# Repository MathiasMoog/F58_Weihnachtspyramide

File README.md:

# Antrieb und LED-Kerzen für Weihnachtspyramide

Und als kurzes Video: [Weihnachtspyramide](Bilder/Pyramide.mp4)

## Kurzfassung

Ein Arduino Nano ESP steuert den Antrieb und die LED Kerzen einer Weihnachtspyramide.

Über den ESP wird eine MQTT Anbindung erstellt.

### Hintergrund

Unsere Weihnachtspyramide ist seit einigen Jahren nicht mehr genutzt worden, da niemand Lust hat auf die echten Kerzen aufzupassen. Außerdem läuft sie mit den Kerzen nicht so gut.

In der Bastelkiste hatte ich noch einen (uralten) [Arduino Nano ESP](https://iot.fkainka.de/board) von F. Kainka und aus dem alten Drucker den Antrieb für die Scan Einheit.

### Ordner

- Bilder - Bilder und Zeichnungen
- Druckvorlagen - OpenSCAD Zeichnungen für 3D Drucke 
- PyramidenMQTT - Der Arduino Sketch 
- PyramidenSchaltplan - KiCad Schaltplan und Platine

## Aufbau

Passt es für eure Weihnachtspyramide an, dieser Abschnitt bezieht sich auf meine Pyramide.

### Antrieb 

Mit einem Motor aus der Bastelkiste probiert. Alter Antriebsmotor aus Scanner mit Getriebe. Blech zurecht gesägt. Optische Drehzahlerfassung entfernt. Anstelle Zahnräder, einen Gummiring verwendet. Letztes Zahnrad am Motor geschliffen so dass eine Laufrille für den Gummiring entsteht.  

Adapter von Antriebsstange über Antriebsrad bis Aufnahme in Kugellager, [Antrieb](Druckvorlagen/Antrieb.scad), und eine Kugellager Halterung,[Grundplatte](Druckvorlagen/Grundplatte.scad),  in OpenScad gezeichnet. Druck in PETG. Material ist guter Kompromiss zwischen leicht auf dem alten Creatity Ender druckbar und ausreichender Festigkeit. 

Antrieb                    |  Grundplatte
:-------------------------:|:-------------------------:
 | 

Der neue Antrieb ersetzt die alte Lagerung in einer Keramikschale.

Vorher                    |  Nachher
:-------------------------:|:-------------------------:
 | 

### Ansteuerung des Motors
  
Der Motor läuft ab 2,5 V an. Bilde 0 bis 100 auf 0 + [128, 255] ab. Er nimmt maximal 80 mA auf. Es reicht ein kleiner Transistor zum Schalten.

Aus Bastelkiste BC 639, 1 A maximal, gemessen Verstärkung hFE 100, Datenblatt mindestens 25 bei 5 mA Basisstrom. Auslegung, 560 Ohm Vorwiderstand

### Kerzen

Auf Thingiverse habe ich Kerzen mit schön gestalteten Flammen gefunden. Sie sind Teil eines Weihnachtsbogens [Christmas Light Bow](https://www.thingiverse.com/thing:4674237) von M. Lachmann. Flamme.stl mit transparentem PLA und die Kerzen in weißem PLA gedruckt. 

Kerze.stl hat Original 10 mm Durchmesser. Ich benötige 13 mm. Skaliere in x und y Richtung um 130 %. In x Richtung Skalierung 70, 80, 90, 100, 110, 120 %. Sieht nach ungleichmäßig abgebrannten Kerzen aus.

Löcher in die original Kerzenhalter gebohrt und Kabel durchgeführt:

Kabelführung                    |  Fertige Kerzen
:-------------------------:|:-------------------------:
 | 

An der Pyramide habe ich die Aussparungen für die Kerzenhalter mit einer Feile um deine Kabeldurchführung vergrößert.

Helle orange LEDs mit 5 mm Druchmesser im Vorrat entdeckt. Mit denen ergibt sich ein warmes Kerzenlicht. Jede LED mit zweiadrigem Kabel (Altes Flachbahn Kabel von Floppy) und 2,5 mm Stecker anbinden.

Vermessen 2,07 V bei 20 mA. Gewählt, 150 Ohm Vorwidderstand bei 5 V Versorgung und 0,5 V Spannungsabfall im ATMEGA.

## Schaltplan und Platine

Die Schaltung ist recht einfach. Motor und LEDs werden mit 5 V aus dem Arduino betrieben.

Aufgebaut habe ich es auf einem Stück Lochraster Platine

Der USB Anschluss und der Taster zur Bedienung ragen etwas unter dem Holzrahmen der Pyramide hervor. Mit dem Taster lassen sich die Kerzen und der Motor ein- und ausschalten.

## Arduino Sketch

Im Code erklärt: [PyramidenMqtt](PyramidenMqtt/PyramidenMqtt.ino)

Die NanoESP Boards sind schon sehr betagt, aber es funktioniert immer noch. Ich habe zwei Anpassungen an der NanoESP Bibliothek vorgenommen: Messages zuschneiden und obsolete subscribe events bei disconnect löschen. Getestet habe ich mit meinem Fork der [NanoESP Bibliothek](https://github.com/MathiasMoog/NanoESP)

Damit 6 LEDs und der Motor per PWM angesteuert werden können, nutze ich für die LEDs die [SoftPWM Bibliothek](https://github.com/bhagman/SoftPWM) von B. Hagman.

Die Konfiguration erfolgt in secrets.h. Eingecheckt ist nur die secretsVorlage.h. In secrets.h umbenennen und anpassen.

## Einbindung in die Hausautomation

Ich nutze [openHAB](https://www.openhab.org/) mit einer textuellen Konfiguration.

Hier die Thing Definition

    Thing mqtt:topic:weihnachtspyramide "Weihnachtspyramide" (mqtt:broker:myBroker) {
      Channels:
      // Motor als Dimmer, 0..100
      Type dimmer : motor "Motor" [ stateTopic="openhab/pyramide/motor/state", commandTopic="openhab/pyramide/motor/set", min=0, max=100, step=1 ]
      // Kerzen als Switch, ON / OFF
      Type switch : kerzen "Kerzen" [ stateTopic="openhab/pyramide/kerzen/state", commandTopic="openhab/pyramide/kerzen/set" ]
    } 
	
Diese gehört in eine Bridge hinein die die Verbindung zu dem MQTT broker beinhaltet.

Die Items zu den beiden channels:

    Group gMqttWeihnachtspyramide "Weihnachtspyramide" <network> (gEG_Buero)

    /* Motor der Weihnachtspyramide.
        Dimmer 0..100
        0 = Aus
        1 = Anlauf, ca. 2.5 V
        100 = Voll an
    */    
    Dimmer PyramideMotor "Motor [%d]" <network> (gMqttWeihnachtspyramide) 
      { channel="mqtt:topic:weihnachtspyramide:motor" }

    /* Kerzen der Weihnachtspyramide.
        Switch Ein/Aus, flackern sobald ein.
    */
    Switch PyramideKerzen "Kerzen" <network> (gMqttWeihnachtspyramide) 
      { channel="mqtt:topic:weihnachtspyramide:kerzen" }

So lässt sich alles vom Handy aus bedienen und die LEDs gehen mit der restlichen Weihnachtsbeleuchtung automatisch an.

## Testen

Zum Testen - und für den Betrieb - wird ein MQTT broker benötigt. Ich verwende den [Mosquitto broker](https://mosquitto.org/) von Eclipse.

Es hat etwas gedauert bis ich eine stabile Lösung mit automatischen Neu-Verbindungen zum WiFi und MQTT beisammen hatte. Ein Blick in die Mosquitto Logs hilft ...

    sudo tail -f /var/log/mosquitto/mosquitto.log

Mittlerweile gehen nur noch sehr selten (während reconnect) MQTT messages verloren, ggf. Prüfen

    mosquitto_sub -h xxx -u xxx -P xxx -t openhab/pyramide/#

## Nachbau

Den NanoESP gibt es schon länger nicht mehr. Der Arduino Nano ESP 32 ist nahezu Pin-Kompatibel. Zu beachten ist:

- Er arbeitet mit 3.3 V, ggf. die LED Vorwiderstände anpassen 
- Mein Motor benötigt 5 V, die können von USB übernommen werden
- Die SoftPWM Bibliothek ist nicht mehr notwendig
- Es wird ein anderer MQTT Client benötigt, z.B. ArduinoMqttClient

Umgesetzt habe ich es nicht, hier ein MQTT Beispiel mit dem Nano ESP 32: [MQTT LED](https://gitlab.com/MathiasMoog/L20_MqttLed)

Ansonsten irgendein günstiges ESP 32 Board ...

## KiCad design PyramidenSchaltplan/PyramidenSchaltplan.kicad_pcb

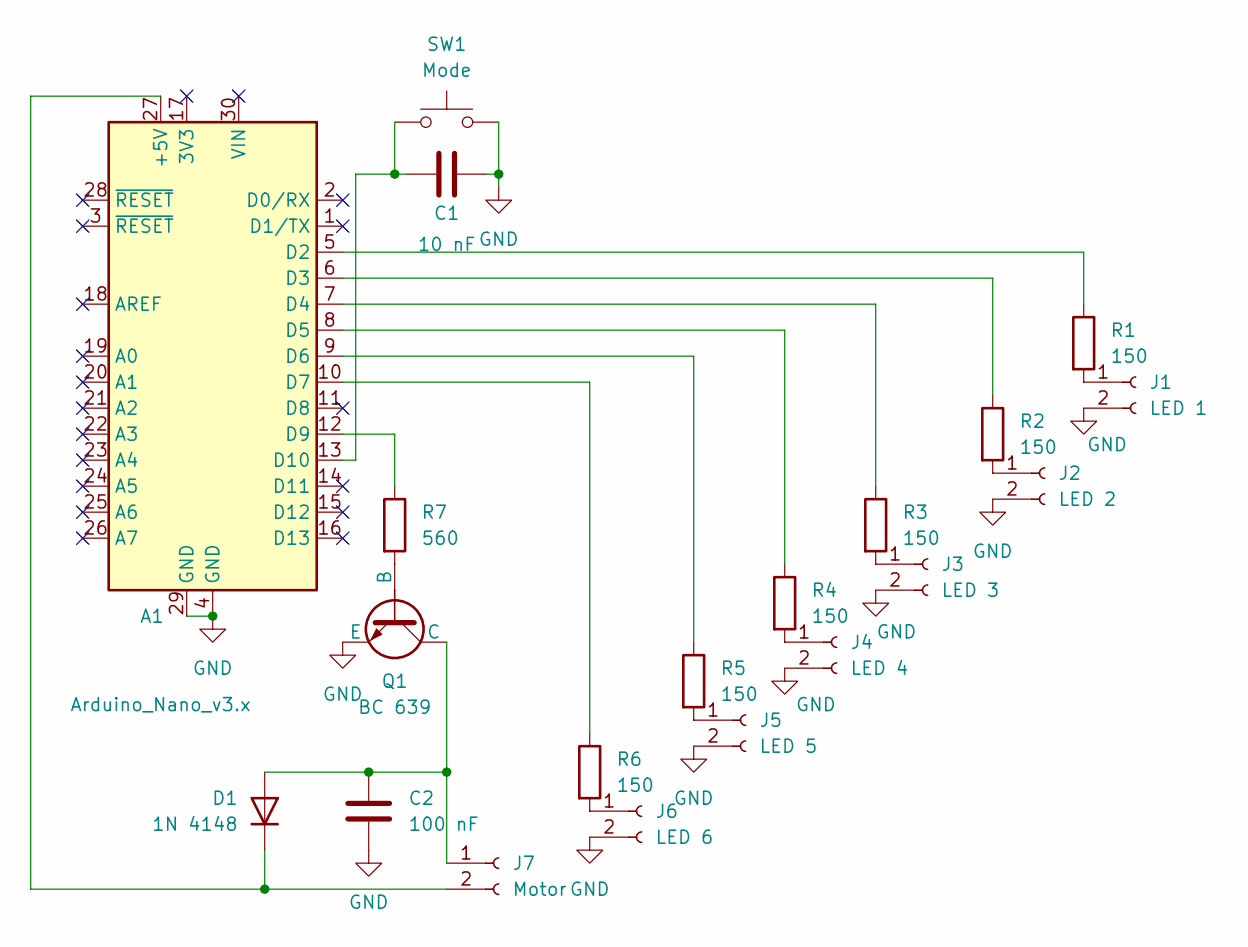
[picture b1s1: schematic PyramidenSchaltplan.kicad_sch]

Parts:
A1: Arduino_Nano_v3.x; Arduino_Nano
C1: 10 nF; C_Disc_D4.7mm_W2.5mm_P5.00mm
C2: 100 nF; C_Disc_D4.7mm_W2.5mm_P5.00mm
D1: 1N 4148; D_5W_P5.08mm_Vertical_AnodeUp
J1: LED 1; PinHeader_1x02_P2.54mm_Vertical
J2: LED 2; PinHeader_1x02_P2.54mm_Vertical
J3: LED 3; PinHeader_1x02_P2.54mm_Vertical
J4: LED 4; PinHeader_1x02_P2.54mm_Vertical
J5: LED 5; PinHeader_1x02_P2.54mm_Vertical
J6: LED 6; PinHeader_1x02_P2.54mm_Vertical
J7: Motor; PinHeader_1x02_P2.54mm_Vertical
Q1: BC 639; TO-92L_HandSolder
R1, R2, R3, R4, R5, R6: 150; R_Axial_DIN0207_L6.3mm_D2.5mm_P5.08mm_Vertical
R7: 560; R_Axial_DIN0207_L6.3mm_D2.5mm_P5.08mm_Vertical
SW1: Mode; SW_Tactile_SPST_Angled_PTS645Vx83-2LFS

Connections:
GND: A1.4 (GND), A1.29 (GND), C1.1, C2.2, J1.2, J2.2, J3.2, J4.2, J5.2, J6.2, Q1.1 (E), SW1.2
unnamed: A1.27 (+5V), D1.1 (K), J7.2
unnamed: A1.5 (D2), R1.1
unnamed: A1.6 (D3), R2.1
unnamed: A1.7 (D4), R3.1
unnamed: A1.8 (D5), R4.1
unnamed: A1.9 (D6), R5.1
unnamed: A1.10 (D7), R6.1
unnamed: A1.12 (D9), R7.1
unnamed: A1.13 (D10), C1.2, SW1.1
unnamed: C2.1, D1.2 (A), J7.1, Q1.2 (C)
unnamed: J1.1, R1.2
unnamed: J2.1, R2.2
unnamed: J3.1, R3.2
unnamed: J4.1, R4.2
unnamed: J5.1, R5.2
unnamed: J6.1, R6.2
unnamed: Q1.3 (B), R7.2

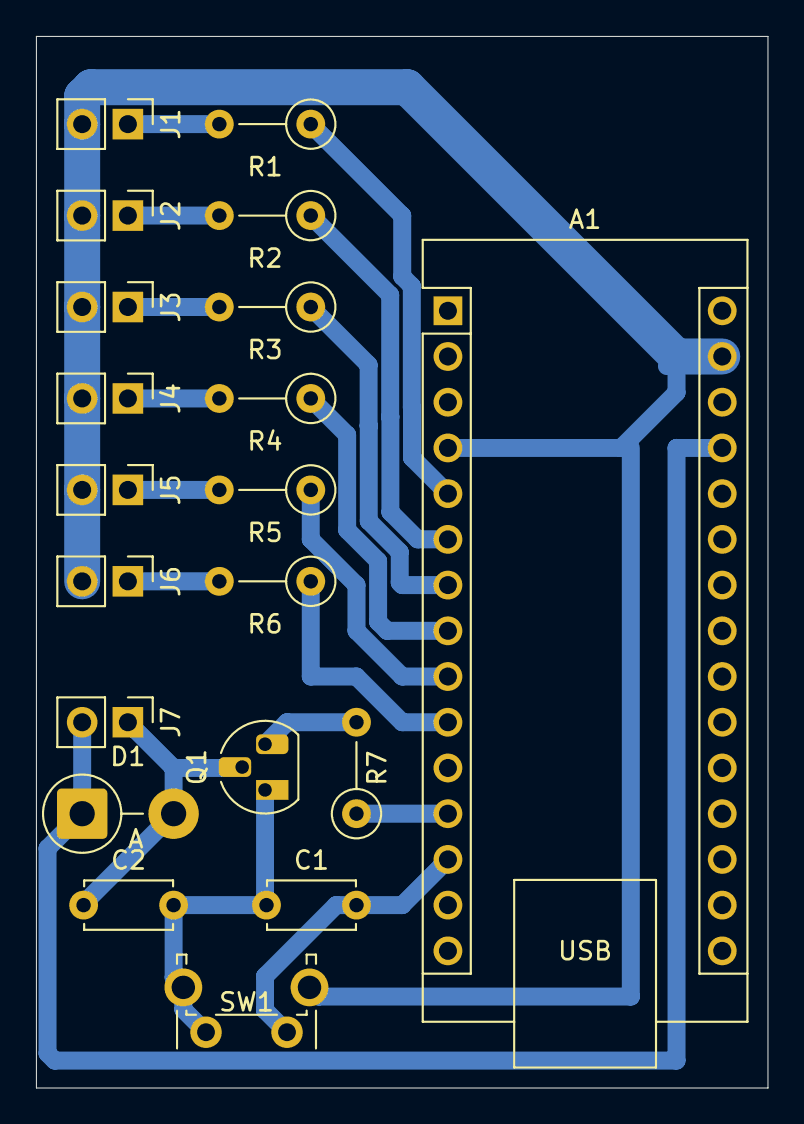
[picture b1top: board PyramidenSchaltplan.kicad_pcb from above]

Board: 2 copper layers, 40.6 x 58.4 mm, 20 parts (0 on the bottom side), 18 nets.

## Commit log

2026-02-21 Pyramide einsatzbereit
2026-02-21 Fix image syntax in README.md
2026-02-21 Dokumentation ergänzt
2026-02-21 Update title to include LED in README
